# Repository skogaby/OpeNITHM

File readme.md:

# OpeNITHM

This branch is entirely work in progress, don't use it.

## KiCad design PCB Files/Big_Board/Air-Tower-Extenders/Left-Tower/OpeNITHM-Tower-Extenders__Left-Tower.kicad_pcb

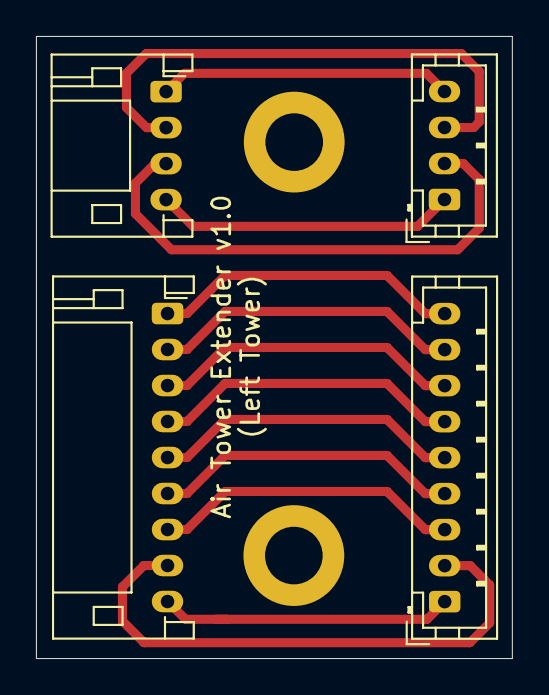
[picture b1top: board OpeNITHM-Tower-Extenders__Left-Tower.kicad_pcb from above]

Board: 2 copper layers, 26.4 x 34.6 mm, 6 parts (0 on the bottom side), 13 nets.

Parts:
H1, H2: MountingHole; MountingHole_3.2mm_M3_DIN965_Pad
J1: Conn_01x04_Male; JST_PH_S4B-PH-K_1x04_P2.00mm_Horizontal
J2: Conn_01x04_Male; JST_PH_B4B-PH-K_1x04_P2.00mm_Vertical
J3: Conn_01x09_Male; JST_PH_S9B-PH-K_1x09_P2.00mm_Horizontal
J4: Conn_01x09_Male; JST_PH_B9B-PH-K_1x09_P2.00mm_Vertical

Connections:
unnamed: J1.1, J2.4
unnamed: J1.2, J2.3
unnamed: J1.3, J2.2
unnamed: J1.4, J2.1
unnamed: J3.1, J4.9
unnamed: J3.2, J4.8
unnamed: J3.3, J4.7
unnamed: J3.4, J4.6
unnamed: J3.5, J4.5
unnamed: J3.6, J4.4
unnamed: J3.7, J4.3
unnamed: J3.8, J4.2
unnamed: J3.9, J4.1

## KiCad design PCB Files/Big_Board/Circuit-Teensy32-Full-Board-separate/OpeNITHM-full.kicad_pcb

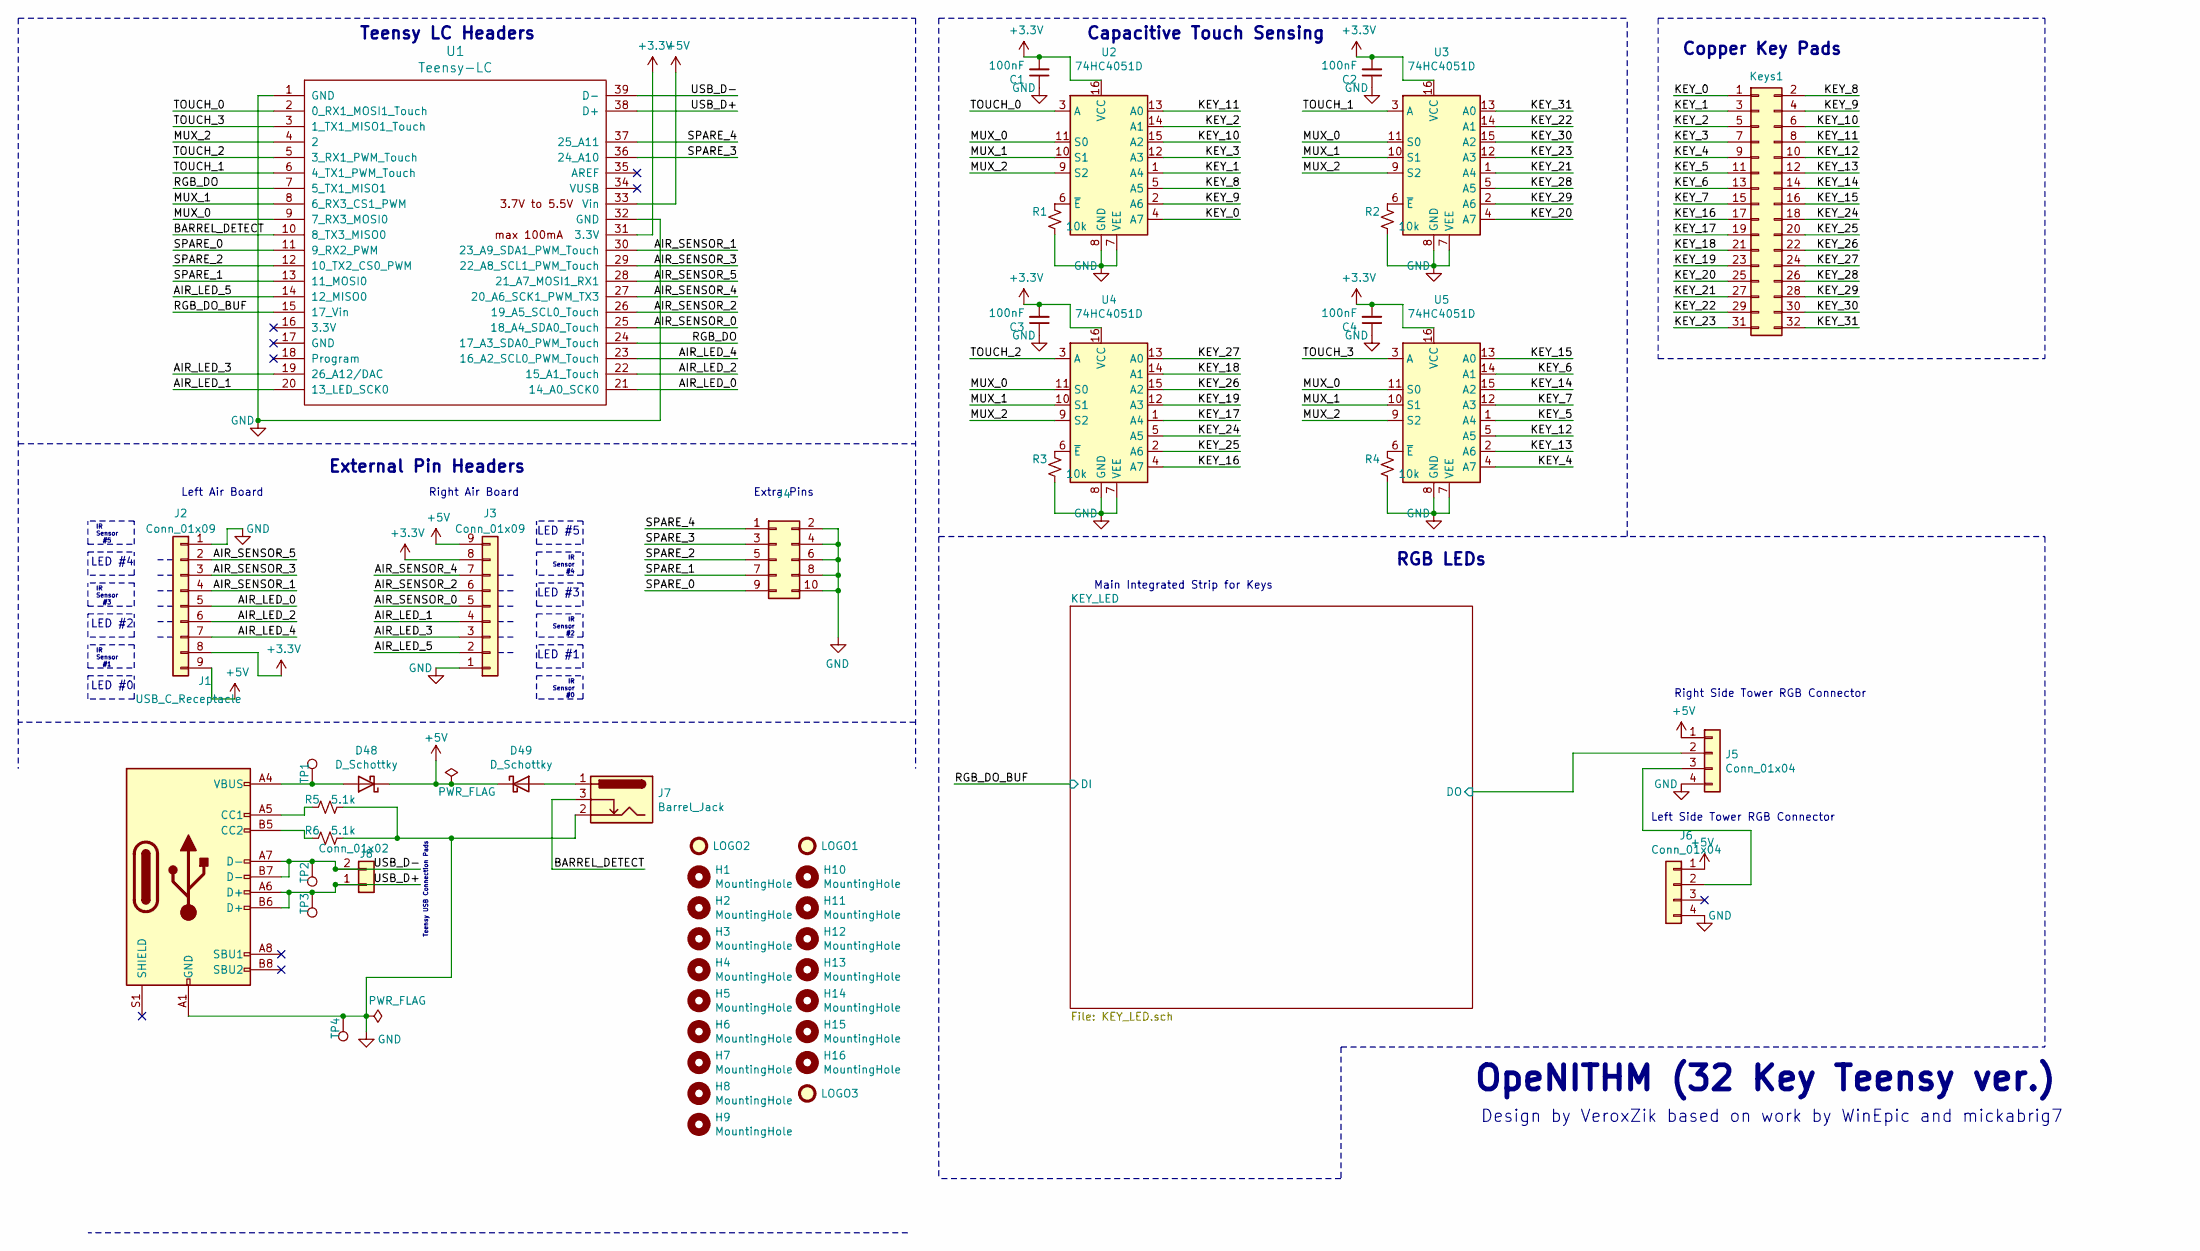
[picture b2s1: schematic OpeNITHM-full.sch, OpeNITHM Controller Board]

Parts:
C1, C2, C3, C4: 100nF; C_0603_1608Metric; LCSC C14663
D48, D49: D_Schottky; D_SMA; LCSC C22452
H1, H2, H3, H4, H5, H6, H7, H8, H9, H10, H11, H12, H13, H14, H15, H16: MountingHole; MountingHole_3.2mm_M3_ISO14580
J1: USB_C_Receptacle; USB_C_Receptacle_GCT_USB4085
J2, J3: Conn_01x09; JST_PH_S9B-PH-K_1x09_P2.00mm_Horizontal
J4: Conn_02x05_Odd_Even; PinHeader_2x05_P2.54mm_Horizontal
J5, J6: Conn_01x04; JST_PH_S4B-PH-K_1x04_P2.00mm_Horizontal
J7: Barrel_Jack; BarrelJack_Horizontal
J8: Conn_01x02; PinHeader_1x02_P2.54mm_Vertical
Keys1: Conn_02x16_Odd_Even; Pads
LOGO1, LOGO3: Logo; openithm-logo
LOGO2: Logo; openithm-big
R1, R2, R3, R4: 10k; R_0603_1608Metric; LCSC C25804
R5, R6: 5.1k; R_0603_1608Metric; LCSC C23186
TP1: +5V; TestPoint_Pad_D1.5mm
TP2: D-; TestPoint_Pad_D1.5mm
TP3: D+; TestPoint_Pad_D1.5mm
TP4: GND; TestPoint_Pad_D1.5mm
U1: Teensy-LC; TeensyLC
U2, U3, U4, U5: 74HC4051D; SOIC-16_3.9x9.9mm_P1.27mm; LCSC C9386

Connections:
+3V3: C1.2, C2.2, C3.2, C4.2, J2.8, J3.8, U1.31 (3.3V), U2.16 (VCC), U3.16 (VCC), U4.16 (VCC), U5.16 (VCC)
+5V: D48.1 (K), D49.1 (K), J2.9, J3.9, J5.1, J6.1, U1.33 (Vin); also elsewhere on the board
/AIR_LED_0: J2.5, U1.21 (14_A0_SCK0)
/AIR_LED_1: J3.4, U1.20 (13_LED_SCK0)
/AIR_LED_2: J2.6, U1.22 (15_A1_Touch)
/AIR_LED_3: J3.3, U1.19 (26_A12/DAC)
/AIR_LED_4: J2.7, U1.23 (16_A2_SCL0_PWM_Touch)
/AIR_LED_5: J3.2, U1.14 (12_MISO0)
/AIR_SENSOR_0: J3.5, U1.25 (18_A4_SDA0_Touch)
/AIR_SENSOR_1: J2.4, U1.30 (23_A9_SDA1_PWM_Touch)
/AIR_SENSOR_2: J3.6, U1.26 (19_A5_SCL0_Touch)
/AIR_SENSOR_3: J2.3, U1.29 (22_A8_SCL1_PWM_Touch)
/AIR_SENSOR_4: J3.7, U1.27 (20_A6_SCK1_PWM_TX3)
/AIR_SENSOR_5: J2.2, U1.28 (21_A7_MOSI1_RX1)
/BARREL_DETECT: J7.3, U1.10 (8_TX3_MISO0)
/KEY_0: Keys1.1, U2.4 (A7)
/KEY_1: Keys1.3, U2.1 (A4)
/KEY_2: Keys1.5, U2.14 (A1)
/KEY_3: Keys1.7, U2.12 (A3)
/KEY_4: Keys1.9, U5.4 (A7)
/KEY_5: Keys1.11, U5.1 (A4)
/KEY_6: Keys1.13, U5.14 (A1)
/KEY_7: Keys1.15, U5.12 (A3)
/KEY_8: Keys1.2, U2.5 (A5)
/KEY_9: Keys1.4, U2.2 (A6)
/KEY_10: Keys1.6, U2.15 (A2)
/KEY_11: Keys1.8, U2.13 (A0)
/KEY_12: Keys1.10, U5.5 (A5)
/KEY_13: Keys1.12, U5.2 (A6)
/KEY_14: Keys1.14, U5.15 (A2)
/KEY_15: Keys1.16, U5.13 (A0)
/KEY_16: Keys1.17, U4.4 (A7)
/KEY_17: Keys1.19, U4.1 (A4)
/KEY_18: Keys1.21, U4.14 (A1)
/KEY_19: Keys1.23, U4.12 (A3)
/KEY_20: Keys1.25, U3.4 (A7)
/KEY_21: Keys1.27, U3.1 (A4)
/KEY_22: Keys1.29, U3.14 (A1)
/KEY_23: Keys1.31, U3.12 (A3)
/KEY_24: Keys1.18, U4.5 (A5)
/KEY_25: Keys1.20, U4.2 (A6)
/KEY_26: Keys1.22, U4.15 (A2)
/KEY_27: Keys1.24, U4.13 (A0)
/KEY_28: Keys1.26, U3.5 (A5)
/KEY_29: Keys1.28, U3.2 (A6)
/KEY_30: Keys1.30, U3.15 (A2)
/KEY_31: Keys1.32, U3.13 (A0)
/KEY_LED/DO: J5.2; also elsewhere on the board
/MUX_0: U1.9 (7_RX3_MOSI0), U2.11 (S0), U3.11 (S0), U4.11 (S0), U5.11 (S0)
/MUX_1: U1.8 (6_RX3_CS1_PWM), U2.10 (S1), U3.10 (S1), U4.10 (S1), U5.10 (S1)
/MUX_2: U1.4 (2), U2.9 (S2), U3.9 (S2), U4.9 (S2), U5.9 (S2)
/RGB_DO: U1.7 (5_TX1_MISO1), U1.24 (17_A3_SDA0_PWM_Touch)
/RGB_DO_BUF: U1.15 (17_Vin); also elsewhere on the board
/SPARE_0: J4.9, U1.11 (9_RX2_PWM)
/SPARE_1: J4.7, U1.13 (11_MOSI0)
/SPARE_2: J4.5, U1.12 (10_TX2_CS0_PWM)
/SPARE_3: J4.3, U1.36 (24_A10)
/SPARE_4: J4.1, U1.37 (25_A11)
/TOUCH_0: U1.2 (0_RX1_MOSI1_Touch), U2.3 (A)
/TOUCH_1: U1.6 (4_TX1_PWM_Touch), U3.3 (A)
/TOUCH_2: U1.5 (3_RX1_PWM_Touch), U4.3 (A)
/TOUCH_3: U1.3 (1_TX1_MISO1_Touch), U5.3 (A)
/USB_D+: J1.A6 (D+), J1.B6 (D+), J8.1, TP3.1, U1.38 (D+)
/USB_D-: J1.A7 (D-), J1.B7 (D-), J8.2, TP2.1, U1.39 (D-)
GND: C1.1, C2.1, C3.1, C4.1, J1.A1 (GND), J1.A12 (GND), J1.B1 (GND), J1.B12 (GND), J2.1, J3.1, J4.2, J4.4, J4.6, J4.8, J4.10, J5.4, J6.4, J7.2, R1.2, R2.2, R3.2, R4.2, R5.1, R6.1, TP4.1, U1.1 (GND), U1.32 (GND), U2.7 (VEE), U2.8 (GND), U3.7 (VEE), U3.8 (GND), U4.7 (VEE), U4.8 (GND), U5.7 (VEE), U5.8 (GND); also elsewhere on the board
unnamed: D48.2 (A), J1.A4 (VBUS), J1.A9 (VBUS), J1.B4 (VBUS), J1.B9 (VBUS), TP1.1
unnamed: D49.2 (A), J7.1
unnamed: J1.A5 (CC1), R5.2
unnamed: J1.B5 (CC2), R6.2
unnamed: J5.3, J6.2
unnamed: R1.1, U2.6 (~E)
unnamed: R2.1, U3.6 (~E)
unnamed: R3.1, U4.6 (~E)
unnamed: R4.1, U5.6 (~E)

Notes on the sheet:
Capacitive Touch Sensing
OpeNITHM (32 Key Teensy ver.)
Design by VeroxZik based on work by WinEpic and mickabrig7
External Pin Headers
Teensy LC Headers
Copper Key Pads
RGB LEDs
Extra Pins
IR Sensor #1
LED #2
IR Sensor #3
LED #0
LED #4
IR Sensor #5
Left Air Board
IR Sensor #0
LED #1
IR Sensor #2
LED #3
IR Sensor #4
LED #5
Right Air Board
Main Integrated Strip for Keys
Right Side Tower RGB Connector
Left Side Tower RGB Connector
Teensy USB Connection Pads

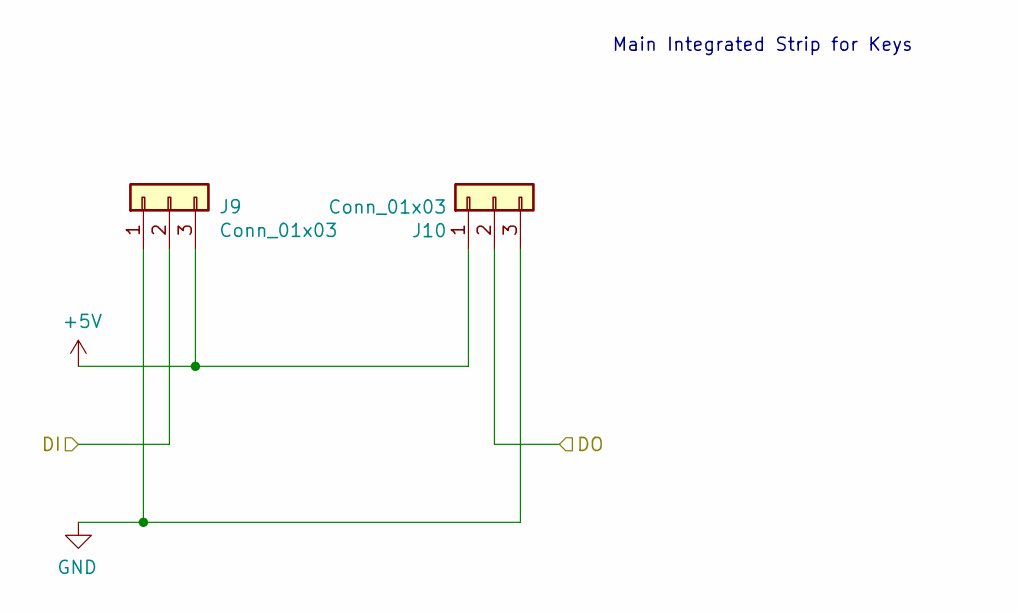
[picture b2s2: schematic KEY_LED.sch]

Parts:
J9, J10: Conn_01x03; PinHeader_1x03_P2.54mm_Vertical

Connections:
+5V: J9.3, J10.1; also elsewhere on the board
/KEY_LED/DO: J10.2; also elsewhere on the board
/RGB_DO_BUF: J9.2; also elsewhere on the board
GND: J9.1, J10.3; also elsewhere on the board

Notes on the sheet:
Main Integrated Strip for Keys

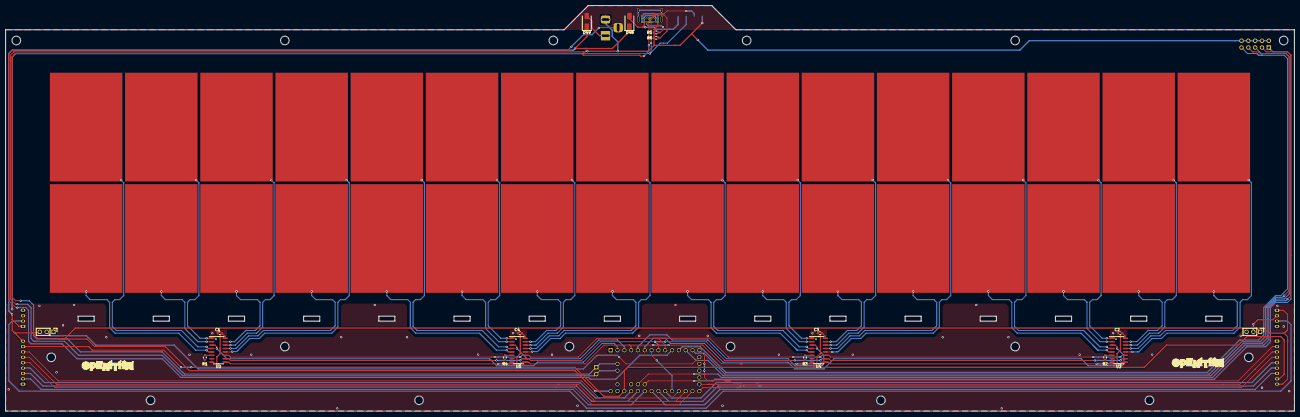
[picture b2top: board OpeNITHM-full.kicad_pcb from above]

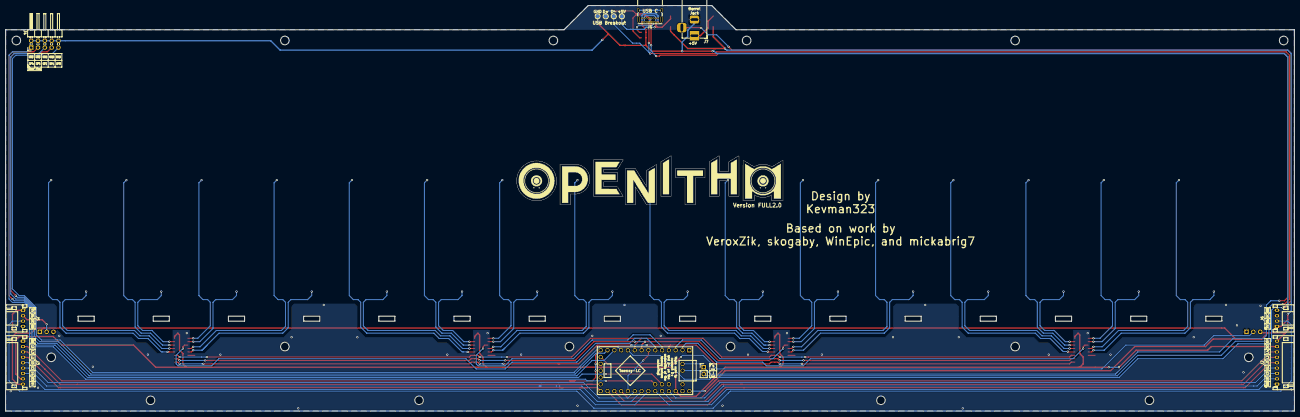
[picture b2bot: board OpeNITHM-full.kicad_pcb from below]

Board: 2 copper layers, 480.0 x 151.0 mm, 51 parts (14 on the bottom side), 74 nets.

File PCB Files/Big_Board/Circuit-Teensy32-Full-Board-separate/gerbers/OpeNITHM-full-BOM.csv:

Comment,Designator,Footprint,LCSC
"100nF","C1,C2,C3,C4","Capacitor_SMD:C_0603_1608Metric","C14663"
"D_Schottky","D48,D49","Diode_SMD:D_SMA","C22452"
"MountingHole","H1,H2,H3,H4,H5,H6,H7,H8,H9,H10,H11,H12,H13,H14,H15,H16","MountingHole:MountingHole_3.2mm_M3_ISO14580",""
"USB_C_Receptacle","J1","Connector_USB:USB_C_Receptacle_GCT_USB4085",""
"Conn_01x09","J2,J3","Connector_JST:JST_PH_S9B-PH-K_1x09_P2.00mm_Horizontal",""
"Conn_02x05_Odd_Even","J4","Connector_PinHeader_2.54mm:PinHeader_2x05_P2.54mm_Horizontal",""
"Conn_01x04","J5,J6","Connector_JST:JST_PH_S4B-PH-K_1x04_P2.00mm_Horizontal",""
"Barrel_Jack","J7","Connector_BarrelJack:BarrelJack_Horizontal",""
"Conn_01x02","J8","Connector_PinHeader_2.54mm:PinHeader_1x02_P2.54mm_Vertical",""
"Conn_01x03","J9,J10","Connector_PinHeader_2.54mm:PinHeader_1x03_P2.54mm_Vertical",""
"Conn_02x16_Odd_Even","Keys1","TouchPad:Pads",""
"Logo","LOGO1,LOGO3","OpeNITHM:openithm-logo",""
"Logo","LOGO2","OpeNITHM:openithm-big",""
"10k","R1,R2,R3,R4","Resistor_SMD:R_0603_1608Metric","C25804"
"5.1k","R5,R6","Resistor_SMD:R_0603_1608Metric","C23186"
"+5V","TP1","TestPoint:TestPoint_Pad_D1.5mm",""
"D-","TP2","TestPoint:TestPoint_Pad_D1.5mm",""
"D+","TP3","TestPoint:TestPoint_Pad_D1.5mm",""
"GND","TP4","TestPoint:TestPoint_Pad_D1.5mm",""
"Teensy-LC","U1","teensy:TeensyLC",""
"74HC4051D","U2,U3,U4,U5","Package_SO:SOIC-16_3.9x9.9mm_P1.27mm","C9386"

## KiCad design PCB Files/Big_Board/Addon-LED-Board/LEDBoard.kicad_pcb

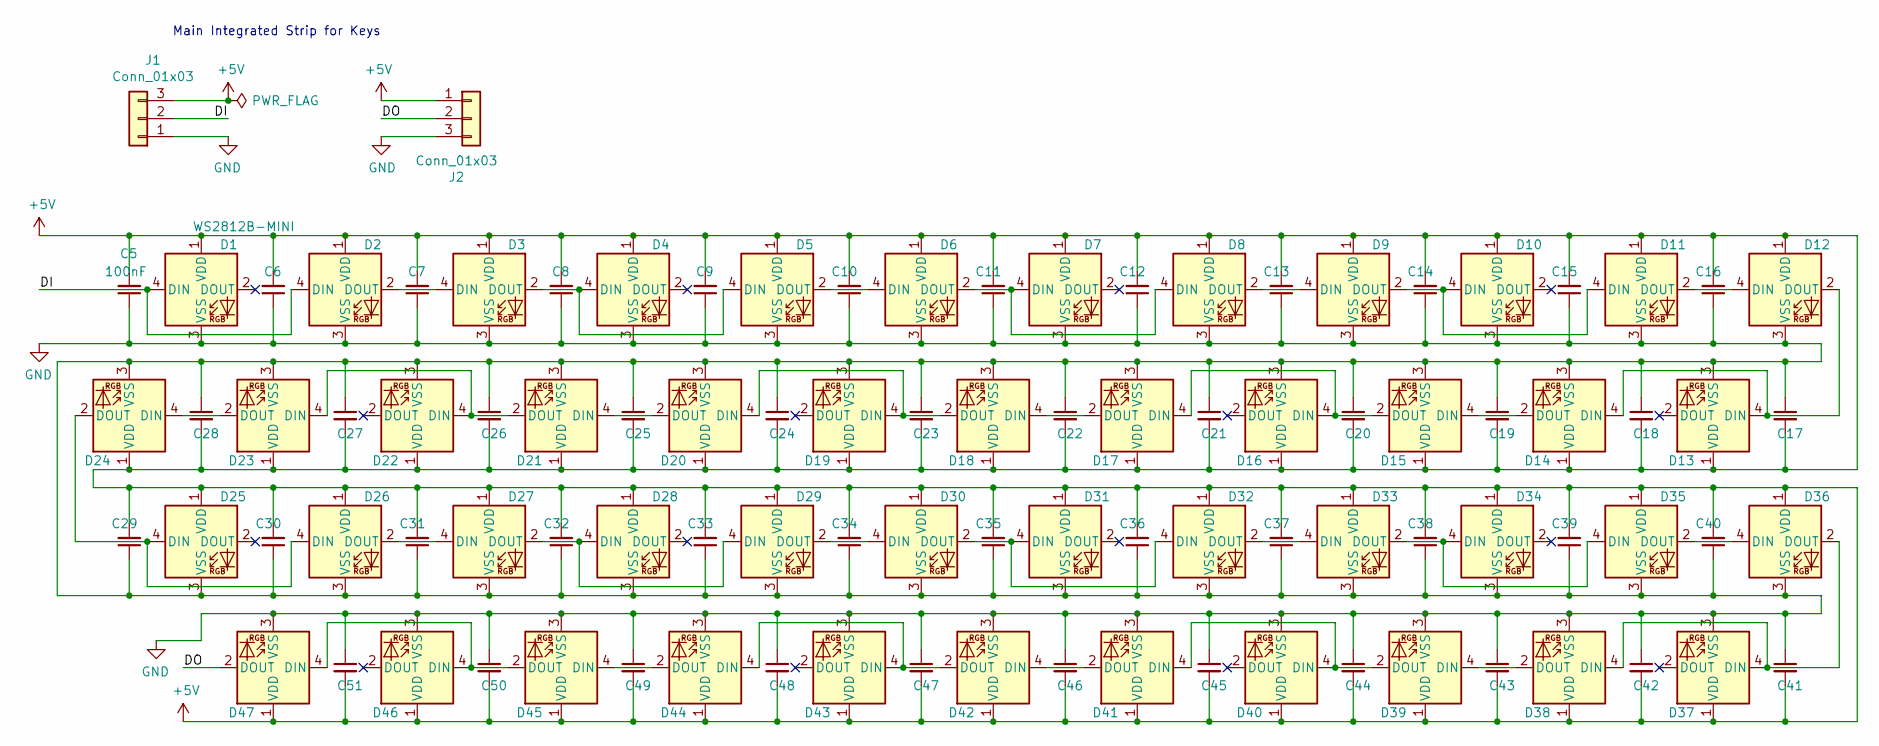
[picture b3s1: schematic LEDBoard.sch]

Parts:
C5, C6, C7, C8, C9, C10, C11, C12, C13, C14, C15, C16, C17, C18, C19, C20, C21, C22, C23, C24, C25, C26, C27, C28, C29, C30, C31, C32, C33, C34, C35, C36, C37, C38, C39, C40, C41, C42, C43, C44, C45, C46, C47, C48, C49, C50, C51: 100nF; C_0603_1608Metric; LCSC C14663
D1, D2, D3, D4, D5, D6, D7, D8, D9, D10, D11, D12, D13, D14, D15, D16, D17, D18, D19, D20, D21, D22, D23, D24, D25, D26, D27, D28, D29, D30, D31, D32, D33, D34, D35, D36, D37, D38, D39, D40, D41, D42, D43, D44, D45, D46, D47: WS2812B-MINI; LED_WS2812B-MINI_LED-4_3535_3.5x3.5mm; LCSC C114583
J1, J2: Conn_01x03; PinHeader_1x03_P2.54mm_Vertical

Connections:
+5V: C5.2, C6.2, C7.2, C8.2, C9.2, C10.2, C11.2, C12.2, C13.2, C14.2, C15.2, C16.2, C17.2, C18.2, C19.2, C20.2, C21.2, C22.2, C23.2, C24.2, C25.2, C26.2, C27.2, C28.2, C29.2, C30.2, C31.2, C32.2, C33.2, C34.2, C35.2, C36.2, C37.2, C38.2, C39.2, C40.2, C41.2, C42.2, C43.2, C44.2, C45.2, C46.2, C47.2, C48.2, C49.2, C50.2, C51.2, D1.1 (VDD), D2.1 (VDD), D3.1 (VDD), D4.1 (VDD), D5.1 (VDD), D6.1 (VDD), D7.1 (VDD), D8.1 (VDD), D9.1 (VDD), D10.1 (VDD), D11.1 (VDD), D12.1 (VDD), D13.1 (VDD), D14.1 (VDD), D15.1 (VDD), D16.1 (VDD), D17.1 (VDD), D18.1 (VDD), D19.1 (VDD), D20.1 (VDD), D21.1 (VDD), D22.1 (VDD), D23.1 (VDD), D24.1 (VDD), D25.1 (VDD), D26.1 (VDD), D27.1 (VDD), D28.1 (VDD), D29.1 (VDD), D30.1 (VDD), D31.1 (VDD), D32.1 (VDD), D33.1 (VDD), D34.1 (VDD), D35.1 (VDD), D36.1 (VDD), D37.1 (VDD), D38.1 (VDD), D39.1 (VDD), D40.1 (VDD), D41.1 (VDD), D42.1 (VDD), D43.1 (VDD), D44.1 (VDD), D45.1 (VDD), D46.1 (VDD), D47.1 (VDD), J1.3, J2.1
/DI: D1.4 (DIN), D2.4 (DIN), J1.2
/DO: D47.2 (DOUT), J2.2
GND: C5.1, C6.1, C7.1, C8.1, C9.1, C10.1, C11.1, C12.1, C13.1, C14.1, C15.1, C16.1, C17.1, C18.1, C19.1, C20.1, C21.1, C22.1, C23.1, C24.1, C25.1, C26.1, C27.1, C28.1, C29.1, C30.1, C31.1, C32.1, C33.1, C34.1, C35.1, C36.1, C37.1, C38.1, C39.1, C40.1, C41.1, C42.1, C43.1, C44.1, C45.1, C46.1, C47.1, C48.1, C49.1, C50.1, C51.1, D1.3 (VSS), D2.3 (VSS), D3.3 (VSS), D4.3 (VSS), D5.3 (VSS), D6.3 (VSS), D7.3 (VSS), D8.3 (VSS), D9.3 (VSS), D10.3 (VSS), D11.3 (VSS), D12.3 (VSS), D13.3 (VSS), D14.3 (VSS), D15.3 (VSS), D16.3 (VSS), D17.3 (VSS), D18.3 (VSS), D19.3 (VSS), D20.3 (VSS), D21.3 (VSS), D22.3 (VSS), D23.3 (VSS), D24.3 (VSS), D25.3 (VSS), D26.3 (VSS), D27.3 (VSS), D28.3 (VSS), D29.3 (VSS), D30.3 (VSS), D31.3 (VSS), D32.3 (VSS), D33.3 (VSS), D34.3 (VSS), D35.3 (VSS), D36.3 (VSS), D37.3 (VSS), D38.3 (VSS), D39.3 (VSS), D40.3 (VSS), D41.3 (VSS), D42.3 (VSS), D43.3 (VSS), D44.3 (VSS), D45.3 (VSS), D46.3 (VSS), D47.3 (VSS), J1.1, J2.3
unnamed: D2.2 (DOUT), D3.4 (DIN)
unnamed: D3.2 (DOUT), D4.4 (DIN), D5.4 (DIN)
unnamed: D5.2 (DOUT), D6.4 (DIN)
unnamed: D6.2 (DOUT), D7.4 (DIN), D8.4 (DIN)
unnamed: D8.2 (DOUT), D9.4 (DIN)
unnamed: D9.2 (DOUT), D10.4 (DIN), D11.4 (DIN)
unnamed: D11.2 (DOUT), D12.4 (DIN)
unnamed: D12.2 (DOUT), D13.4 (DIN), D14.4 (DIN)
unnamed: D14.2 (DOUT), D15.4 (DIN)
unnamed: D15.2 (DOUT), D16.4 (DIN), D17.4 (DIN)
unnamed: D17.2 (DOUT), D18.4 (DIN)
unnamed: D18.2 (DOUT), D19.4 (DIN), D20.4 (DIN)
unnamed: D20.2 (DOUT), D21.4 (DIN)
unnamed: D21.2 (DOUT), D22.4 (DIN), D23.4 (DIN)
unnamed: D23.2 (DOUT), D24.4 (DIN)
unnamed: D24.2 (DOUT), D25.4 (DIN), D26.4 (DIN)
unnamed: D26.2 (DOUT), D27.4 (DIN)
unnamed: D27.2 (DOUT), D28.4 (DIN), D29.4 (DIN)
unnamed: D29.2 (DOUT), D30.4 (DIN)
unnamed: D30.2 (DOUT), D31.4 (DIN), D32.4 (DIN)
unnamed: D32.2 (DOUT), D33.4 (DIN)
unnamed: D33.2 (DOUT), D34.4 (DIN), D35.4 (DIN)
unnamed: D35.2 (DOUT), D36.4 (DIN)
unnamed: D36.2 (DOUT), D37.4 (DIN), D38.4 (DIN)
unnamed: D38.2 (DOUT), D39.4 (DIN)
unnamed: D39.2 (DOUT), D40.4 (DIN), D41.4 (DIN)
unnamed: D41.2 (DOUT), D42.4 (DIN)
unnamed: D42.2 (DOUT), D43.4 (DIN), D44.4 (DIN)
unnamed: D44.2 (DOUT), D45.4 (DIN)
unnamed: D45.2 (DOUT), D46.4 (DIN), D47.4 (DIN)

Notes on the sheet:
Main Integrated Strip for Keys

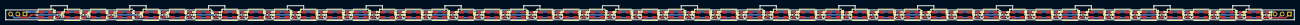
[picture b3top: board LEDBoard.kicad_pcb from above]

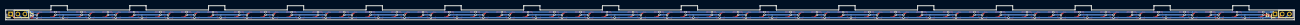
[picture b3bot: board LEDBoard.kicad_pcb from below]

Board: 2 copper layers, 458.0 x 5.0 mm, 96 parts (2 on the bottom side), 34 nets.

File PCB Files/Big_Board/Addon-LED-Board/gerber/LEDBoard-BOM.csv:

Comment,Designator,Footprint,LCSC
"100nF","C5,C6,C7,C8,C9,C10,C11,C12,C13,C14,C15,C16,C17,C18,C19,C20,C21,C22,C23,C24,C25,C26,C27,C28,C29,C30,C31,C32,C33,C34,C35,C36,C37,C38,C39,C40,C41,C42,C43,C44,C45,C46,C47,C48,C49,C50,C51","Capacitor_SMD:C_0603_1608Metric","C14663"
"WS2812B-MINI","D1,D2,D3,D4,D5,D6,D7,D8,D9,D10,D11,D12,D13,D14,D15,D16,D17,D18,D19,D20,D21,D22,D23,D24,D25,D26,D27,D28,D29,D30,D31,D32,D33,D34,D35,D36,D37,D38,D39,D40,D41,D42,D43,D44,D45,D46,D47","LED_SMD:LED_WS2812B-MINI_LED-4_3535_3.5x3.5mm","C114583"
"Conn_01x03","J1,J2","Connector_PinHeader_2.54mm:PinHeader_1x03_P2.54mm_Horizontal",""

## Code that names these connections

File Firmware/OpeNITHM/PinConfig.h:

#include "Config.h"

#ifndef _PINCONFIG_h
#define _PINCONFIG_h

// Multiplexer pin settings
#if defined(OPENITHM_V1_0)
#define MUX_0 20
#define MUX_1 19
#define MUX_2 18
#elif defined(OPENITHM_V1_1)
#define MUX_0 2
#define MUX_1 1
#define MUX_2 0
#elif defined(OPENITHM_V2_0)
#define MUX_0 0
#define MUX_1 1
#define MUX_2 2
#elif defined(OPENITHM_V2_1)
#define MUX_0 2
#define MUX_1 3
#define MUX_2 4
#elif defined(OPENITHM_FULL_V1_0)
#define MUX_0 4
#define MUX_1 3
#define MUX_2 2
#elif defined(OPENITHM_FULL_V2_0)
#define MUX_0 7
#define MUX_1 6
#define MUX_2 2
#endif

// Sensor pin settings
#if defined(OPENITHM_V1_0)
#define LED_0 16
#define LED_1 21
#define LED_2 5
#elif defined(OPENITHM_V1_1) || defined(OPENITHM_V2_0)
#define LED_0 7
#define LED_1 6
#define LED_2 5
#elif defined(OPENITHM_V2_1) || defined(OPENITHM_FULL_V1_0)
#define LED_0 8
#define LED_1 7
#define LED_2 6
#elif defined(OPENITHM_FULL_V2_0)
#define LED_0 14
#define LED_1 13
#define LED_2 15
#define LED_3 26
#define LED_4 16
#define LED_5 12
#endif

#ifdef IR_SENSOR_MULTIPLEXED
#define SENSOR_IN A0
#else
#if defined(OPENITHM_V1_0)
#define AIR_SENSOR_0_PIN 10
#define AIR_SENSOR_1_PIN 11
#define AIR_SENSOR_2_PIN 12
#define AIR_SENSOR_3_PIN 6
#define AIR_SENSOR_4_PIN 8
#define AIR_SENSOR_5_PIN 9
#elif defined(OPENITHM_V1_1)
#define AIR_SENSOR_0_PIN 20
#define AIR_SENSOR_1_PIN 19
#define AIR_SENSOR_2_PIN 18
#define AIR_SENSOR_3_PIN 23
#define AIR_SENSOR_4_PIN 22
#define AIR_SENSOR_5_PIN 21
#elif defined(OPENITHM_V2_0) || defined(OPENITHM_V2_1) || defined(OPENITHM_FULL_V1_0)
#define AIR_SENSOR_0_PIN 18
#define AIR_SENSOR_1_PIN 20
#define AIR_SENSOR_2_PIN 22
#define AIR_SENSOR_3_PIN 19
#define AIR_SENSOR_4_PIN 21
#define AIR_SENSOR_5_PIN 23
#elif defined(OPENITHM_FULL_V2_0)
#define AIR_SENSOR_0_PIN 18
#define AIR_SENSOR_1_PIN 23
#define AIR_SENSOR_2_PIN 19
#define AIR_SENSOR_3_PIN 22
#define AIR_SENSOR_4_PIN 20
#define AIR_SENSOR_5_PIN 21
#endif
#endif

// Capsense pin settings
#if defined(OPENITHM_V1_0)
#define TOUCH_0 22
#define TOUCH_1 23
#elif defined(OPENITHM_V1_1)
#define TOUCH_0 16
#define TOUCH_1 3
#elif defined(OPENITHM_V2_0)
#define TOUCH_0 16
#define TOUCH_1 3
#define TOUCH_2 4
#define TOUCH_3 15
#elif defined(OPENITHM_V2_1)
#define TOUCH_0 16
#define TOUCH_1 0
#define TOUCH_2 1
#define TOUCH_3 15
#elif defined(OPENITHM_FULL_V1_0)
#define TOUCH_0 1
#define TOUCH_1 15
#define TOUCH_2 16
#define TOUCH_3 0
#elif defined(OPENITHM_FULL_V2_0)
#define TOUCH_0 0
#define TOUCH_1 4
#define TOUCH_2 3
#define TOUCH_3 1
#endif

// Lighting pin settings
#ifdef USE_DMA_RGB
  #define LED_TYPE    WS2812SERIAL
  #define LED_ORDER   BRG
#else
  #define LED_TYPE    WS2812B
  #define LED_ORDER   GRB
#endif

#if defined(OPENITHM_V1_0)
  #define RGBPIN 4
#elif defined(OPENITHM_V1_1) || defined(OPENITHM_V2_0)
    #ifdef USE_DMA_RGB
       #define RGBPIN 24
    #else
       #define RGBPIN 11
    #endif
#elif defined(OPENITHM_V2_1) || defined(OPENITHM_FULL_V1_0) || defined(OPENITHM_FULL_V2_0)
  #define RGBPIN 5
#endif

#endif  // _PINCONFIG_h

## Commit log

2020-12-21 Fix for two finger presses not working on 16k.
    Before, if a key was already being pressed, it would not check for increased pressure to go from single to double press.
    Now if the key is currently single pressed, it checks if the threshold for double press has been passed.
    The delta threshold for 16k has also been increased, as the previous one was too low and was giving double press even for only one finger.
2021-02-27 Preliminary Big Board V2 changes
2021-03-05 Update readme
    Update readme to fill in the configuring and power on sections
2021-03-05 Backout accidentally committed config changes
2021-03-07 Committing the big board files, and the air tower extender PCBs
2021-03-13 Update the gerbers for the air extender PCBs
